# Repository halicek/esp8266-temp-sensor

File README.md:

# ESP8266 temperature sensor for IoT
Wireless temperature sensor to be used in your next IoT project. :) Quite low consumption, months with single 18650 cell.

## Features:
- Wireless connectivity (ESP8266 12E)
- SHT30 temperature sensor
- low voltage cut-off
- I2C and other free pins accessible via pads
- approx 47 mm x 19 mm size (including 12E)
- position for smd resetable fuse (not used on my prototype)

## Used IOs:
- ESP8266 12E uController
- Sensirion SHT30 temperature sensor
- STM1061 3.4 V voltage monitor
- MCP1603T 3.3 V synchronous buck voltage regulator

Why so high voltage cut-off? It seems that around 3.0 V input regulator will not supply enough power for ESP8266 to perform well so this regulator meant for 3.3V power level seems appropriate. Please prove how wrong I am! :) 

## Used firmware:
ESP Easy. https://www.letscontrolit.com/wiki/index.php/ESPEasy Tested and working with ESPEasy Mega package 20190511. The SHT330 support is currently only in test branch, so I recommend using "ESP_Easy_mega-20190511_test_core_260_sdk222_alpha_ESP8266_4M.bin" firmware. Caution: Your ESP8266 may not boot or work properly when started in AP mode, I recommend to supply the credentials via post-flash actions in ESP Easy Flasher or via Serial interface (more fun, don!t forget to "Save" the changes.)

## Bill of materials:
I have used Farnell for nearly all of my purchases. Only inductors were purchased on TME.eu (just because I've purchased bad ones with low Isat and the shipping from Farnell was too high.)

- 1x (5 in package) Snap-on battery contact - 3029803 (bigger were out of stock)
- 2x SKRBAGE010 SWITCH, 1.1N, 4.8X4.8MM, LOW PROFILE - 2056852

- 1x EEEFT0J221AR CAP, 220µF, 6.3V, RADIAL, SMD - 2065953
- 1x EEE0JA101WR CAP, 100µF, 6.3V, SMD - 2807989
- 1x MC0805X475K100CT CAP, 4.7µF, 10V, 10%, X5R, 0805

- 1x SHT30-DIS-P2.5KS HUMIDITY/TEMP SENSOR, DIGITAL, DFN-8 - 2886652
- 1x STM1061N34WX6F MPU SUPERVISOR/MONITOR - 3129930
- 1x MCP1603T-330I/OS V REG, SYNCH BUCK 0.5A, SMD - 1439373

- 5x RC0805FR-0710KL RES, 10K, 1%, 0.125W, 0805 - 9237755
- 2x CRGH0805F4K7 RES, 4K7, 1%, 0.33W, 0805 - 2332080

- 1x Inductor from TME.eu - 0603 SMD, 4.7 uH, 600mA Isat - NL03JTC4R7 (you generally need an inductor with parameters recommended in MCP1603T datasheet).

## Warning:
There could be some libraries missing in the project. Let me know, I will fix this as I am still learning with kicad and this is my first published project. Just let me know.

## Status

**As of today (July 2019) this is working prototype, third generation of board design with three working prototypes in my flat. Anyway, build at your own risk! And do not forget that 18650 cells can burn too!**

## What I need to finish:
- 3D printed case - i have some preliminary holder for 18650 cell. - https://github.com/halicek/esp8266-temp-sensor/blob/master/Temp-sensor-case-v1.stl

## License:
This is open hardware, use, make, modify. Just let me know any improvement. I will welcome any fix or upgrade. Thank you!

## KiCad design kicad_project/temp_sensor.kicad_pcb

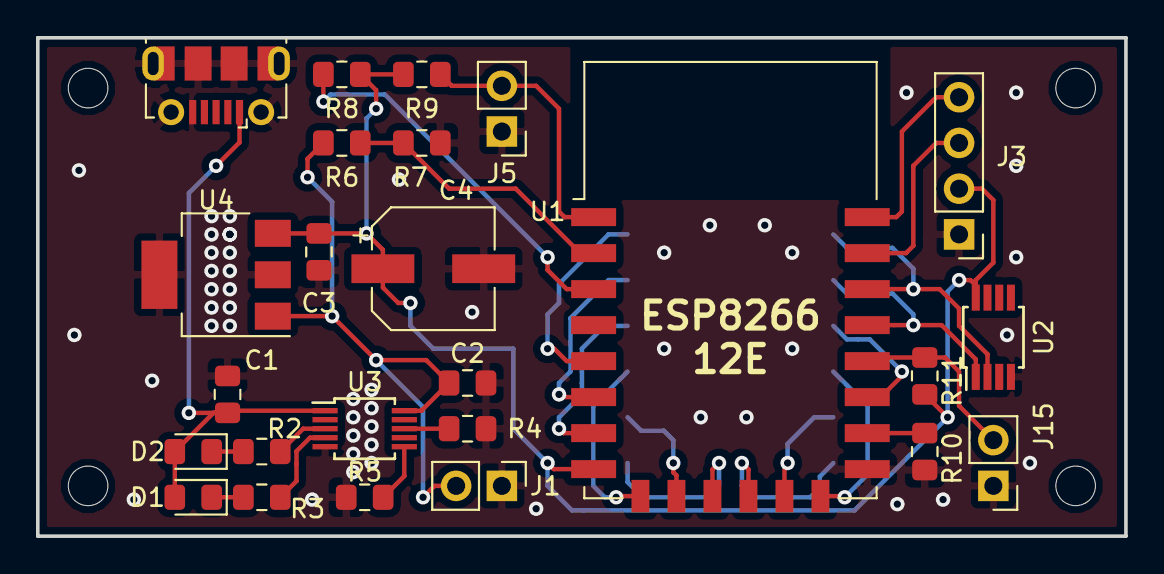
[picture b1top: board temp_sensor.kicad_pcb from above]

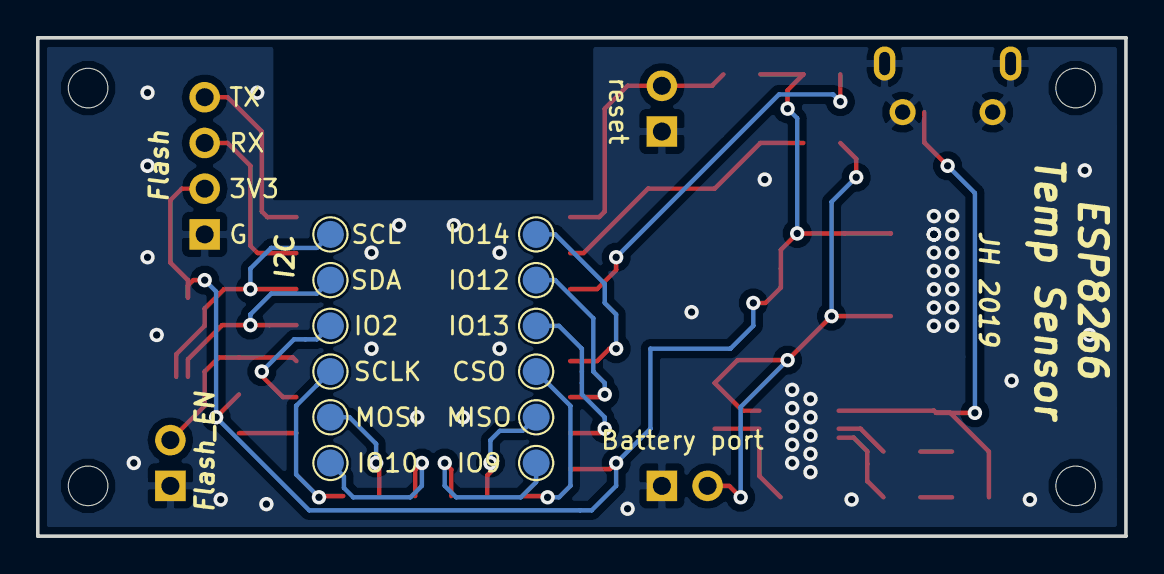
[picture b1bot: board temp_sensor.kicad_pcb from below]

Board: 2 copper layers, 60.5 x 27.7 mm, 37 parts (12 on the bottom side), 29 nets.

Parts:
C1, C3: 1uF; C_0805_2012Metric_Pad1.15x1.40mm_HandSolder
C2: 100uF; C_0805_2012Metric_Pad1.15x1.40mm_HandSolder
C4: 330uF; CP_Elec_6.3x9.9
D1: S2; LED_0805_2012Metric_Pad1.15x1.40mm_HandSolder
D2: S1; LED_0805_2012Metric_Pad1.15x1.40mm_HandSolder
IO13: pad; TestPoint_Pad_D1.5mm
J1: Battery port; PinHeader_1x02_P2.54mm_Vertical
J2: USB_B_Micro; USB_Micro-B_Molex-105017-0001
J3: Flashing; PinHeader_1x04_P2.54mm_Vertical
J5: reset; PinHeader_1x02_P2.54mm_Vertical
J6: CSO; TestPoint_Pad_D1.5mm
J7: MISO; TestPoint_Pad_D1.5mm
J8: IO9; TestPoint_Pad_D1.5mm
J9: IO10; TestPoint_Pad_D1.5mm
J10: MOSI; TestPoint_Pad_D1.5mm
J11: SCLK; TestPoint_Pad_D1.5mm
J12: IO14; TestPoint_Pad_D1.5mm
J13: IO12; TestPoint_Pad_D1.5mm
J14: IO2; TestPoint_Pad_D1.5mm
J15: flash; PinHeader_1x02_P2.54mm_Vertical
J16: SDA; TestPoint_Pad_D1.5mm
J17: SCL; TestPoint_Pad_D1.5mm
R2, R3: 470R; R_0805_2012Metric_Pad1.15x1.40mm_HandSolder
R4, R5, R8, R9, R10, R11: 10k; R_0805_2012Metric_Pad1.15x1.40mm_HandSolder
R6: 330k; R_0805_2012Metric_Pad1.15x1.40mm_HandSolder
R7: 100k; R_0805_2012Metric_Pad1.15x1.40mm_HandSolder
U1: ESP-12E
U2: MCP9808_MSOP; MSOP-8_3x3mm_P0.65mm
U3: MCP73833; MSOP-10_3x3mm_P0.5mm
U4: TC1262-33; SOT-223-3_TabPin2

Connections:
+3V3: C3.1, C4.1, J3.2, R8.2, R9.1, R11.1, U1.8, U2.8, U4.3
+5V: C1.1, D1.2, D2.2, J2.1, U3.1
+BATT: C2.1, J1.2, R6.1, U3.10, U4.1
Earth: C1.2, C2.2, C3.2, C4.2, J1.1, J2.5, J2.6, J3.1, J5.1, J15.1, R4.1, R5.1, R7.1, R10.1, U1.15, U2.4, U3.5, U4.2
unnamed: D1.1, R3.2
unnamed: D2.1, R2.2
unnamed: IO13.1, U1.7
unnamed: J3.3, U1.21
unnamed: J3.4, U1.22
unnamed: J5.2, R9.2, U1.1, U1.4
unnamed: J6.1, U1.9
unnamed: J7.1, U1.10
unnamed: J8.1, U1.11
unnamed: J9.1, U1.12
unnamed: J10.1, U1.13
unnamed: J11.1, U1.14
unnamed: J12.1, U1.5
unnamed: J13.1, U1.6
unnamed: J14.1, U1.17
unnamed: J15.2, R11.2, U1.18
unnamed: J16.1, U1.19, U2.1
unnamed: J17.1, U1.20, U2.2
unnamed: R2.1, U3.3
unnamed: R3.1, U3.4
unnamed: R4.2, U3.8
unnamed: R5.2, U3.6
unnamed: R6.2, R7.2, U1.2
unnamed: R8.1, U1.3
unnamed: R10.2, U1.16

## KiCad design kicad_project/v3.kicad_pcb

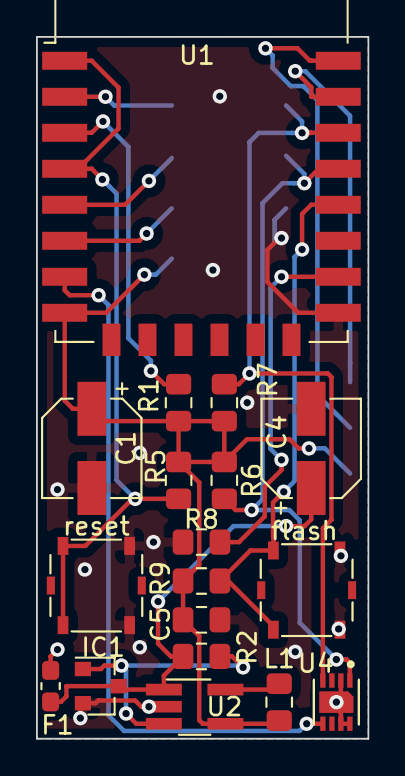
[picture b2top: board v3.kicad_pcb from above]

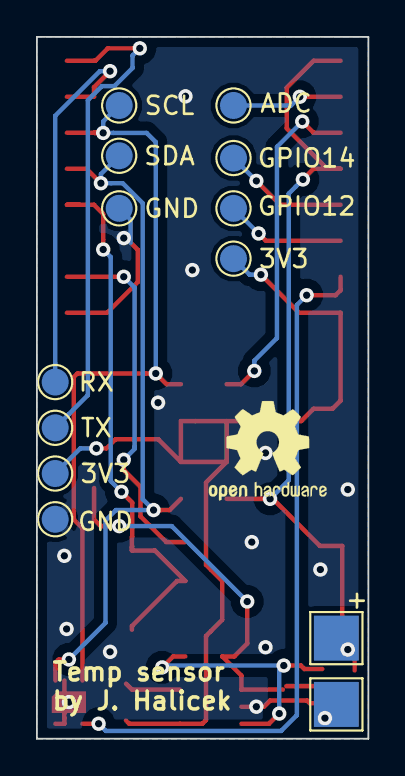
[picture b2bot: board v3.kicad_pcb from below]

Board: 2 copper layers, 18.4 x 39.0 mm, 31 parts (13 on the bottom side), 18 nets.

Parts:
+: BAT+; TestPoint_Pad_2.5x2.5mm
C1: 100uF; CP_Elec_5x5.3
C4: 200 uF; CP_Elec_5x5.3
C5: 4.7-22 uF; C_0805_2012Metric_Pad1.15x1.40mm_HandSolder
F1: Polyfuse; Fuse_0603_1608Metric_Pad1.05x0.95mm_HandSolder
IC1: STM1061; SOT-23
IO1: GPIO14; TestPoint_Pad_D1.5mm
IO2: GPIO12; TestPoint_Pad_D1.5mm
IO3: ADC; TestPoint_Pad_D1.5mm
J2, J9: 3V3; TestPoint_Pad_D1.5mm
J3, J10: GND; TestPoint_Pad_D1.5mm
J4: SDA; TestPoint_Pad_D1.5mm
J5: SCL; TestPoint_Pad_D1.5mm
J6: BAT-; TestPoint_Pad_2.5x2.5mm
J7: TX; TestPoint_Pad_D1.5mm
J8: RX; TestPoint_Pad_D1.5mm
L1: 4.7 uH; L_0805_2012Metric_Pad1.15x1.40mm_HandSolder
R1, R2, R5, R8, R9: 10k; R_0805_2012Metric_Pad1.15x1.40mm_HandSolder
R6, R7: 4k7; R_0805_2012Metric_Pad1.15x1.40mm_HandSolder
U1: ESP-12E
U2: MCP1603T-330I_OS; TSOT-23-5_HandSoldering
U4: SHT31-DIS-B; SON50P250X250X100-9N
flash: SW_flash; SW_SPST_Panasonic_EVQPL_3PL_5PL_PT_A08
reset: SW_reset; SW_SPST_Panasonic_EVQPL_3PL_5PL_PT_A08

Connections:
+3V3: C1.1, C5.1, J2.1, J9.1, L1.2, R1.2, R5.1, R6.2, R7.2, R9.1, U1.8, U2.4
+BATT: C4.1, F1.2, IC1.3, R2.2, U2.1
Earth: C1.2, C4.2, C5.2, IC1.2, J3.1, J6.1, J10.1, R8.1, U1.15, U2.2, U4.2, U4.7, U4.8, U4.9, flash.2, reset.2
unnamed: +.1, F1.1
unnamed: IC1.1, R2.1, U2.3
unnamed: IO1.1, U1.5
unnamed: IO2.1, U1.6
unnamed: IO3.1, U1.2
unnamed: J4.1, R6.1, U1.19, U4.1
unnamed: J5.1, R7.1, U1.20, U4.4
unnamed: J7.1, U1.22
unnamed: J8.1, U1.21
unnamed: L1.1, U2.5
unnamed: R1.1, U1.3
unnamed: R5.2, U1.1, U1.4, reset.1
unnamed: R8.2, U1.16
unnamed: R9.2, U1.18, flash.1
unnamed: U1.7, U4.5

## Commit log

2019-01-04 Initial commit (PCB version 0.9).
    First complete version of Temp Sensor with ESP8266. My second (first bigger one) project in Kicad, please be kind. :)
2019-01-04 sync with my local version
2019-07-26 Visualization of the board.
2019-07-26 Updated project files and gerber data
2019-07-26 Create readme-pcb
2019-07-26 Rename readme-pcb to README-PCB
